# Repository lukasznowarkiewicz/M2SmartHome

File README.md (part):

# M2SmartHome

## Overview

Setting up a smart home hub, such as running Home Assistant, often requires hardware with sufficient performance and connectivity options. Many existing solutions, like Raspberry Pi, may be insufficient for advanced automation tasks due to a low-power CPU or a slow microSD card on which the OS is installed. A good alternative could be an x86 mini PC, but these often lack expansion ports.  

M2SmartHome is an add-on card that operates on PCIe 2.0 x1 and can be installed in any M.2 2280 Key M-equipped device. By integrating multiple essential components into a single device, it eliminates the need for external adapters and additional hardware.  

The device is equipped with onboard eMMC memory, an SD card reader, WiFi 802.11n 2.4GHz radio (RTL8188), and a Thread radio (EFR32) from Silicon Labs. Once installed in an M.2 slot, it provides both storage for the operating system and enhanced connectivity, making it an ideal choice for smart home setups.

## Features

- **Form Factor**: M.2 2280 Key M
- **Interface**: M.2 edge conenctor PCIe 2.0 x1 
- **Storage**: Onboard 16GB eMMC, micro SD card reader
- **Wireless Connectivity**:
  - **WiFi**: 802.11n 2.4GHz (Realtek RTL8188)
  - **Thread Radio**: EFR32MG21 (Silicon Labs)

## Block diagram

On the diagram below siplified system architecture has been presented. PCIe 2.0 x1 interface from host device is connected to PCIe bridge. To four USB 2.0 ports all crucial components are connected: eMMC memory controller, micro SD card controller, USB to UART bridge with Thread / ZigBee RF SOC and WiFi network card. 

### PCie to USB bridge
As a PCIe bridge choosen the `TUSB7340` manufactured by Texas Instruments. `TUSB7340` is a PCIe-to-USB 3.0 host controller with a single line  PCIe interface, compliant with the PCIe  Specification 2.0, supporting programmable driver current, de-emphasis levels, and advanced power management (L0, L0s, L1, L2, L2/L3Ready, L3, D0, D3Hot, D3Cold). It features four USB 3.0 ports as well as USB 2.0 data lines with EHCI (480 Mbps) and OHCI (12 Mbps, 1.5 Mbps) controllers for high-, full-, and low-speed transactions. An EEPROM connected via I²C has been added to enable optional features and configurable settings. Additionally TagConnect TC2030 6-pin connector has been added for flashing I²C EEPROM and TC2050 10-pin connector for accesing `TUSB7340` JTAG.

Components related to this part of the schematic has been highlighted in green on the board view:

### eMMC memory with controller

The `USB2244` is connected to a `TUSB7340` PCIe-to-USB bridge, acting as a USB 2.0-to-eMMC controller for Kingston’s `EMMC16G-MW28-01E10`, with a Microchip `24AA04T-I/OT` EEPROM for optional configuration. The eMMC is powered directly from the M.2 3.3V rail, eliminating the need for an LDO. The eMMC interface uses D0–D8, CMD, and CLK lines, with 49.9kΩ pull-ups on CMD and data lines. The EEPROM is connected via I²C (SCL, SDA) with 4.7kΩ pull-ups, storing configuration settings for the USB controller. This setup provides high-speed eMMC access over USB in an M.2 form factor.

### micro SD card reader and controller

The `USB2244` controller interfaces with a Hirose `DM3AT-SF-PEJM5` push-push microSD card slot and with a Microchip `24AA04T-I/OT` EEPROM for configuration storage. The microSD card is powered by the internal 3.3V regulator of the `USB2244`. The SD interface utilizes CLK, CMD, and D0–D3 lines, with 49.9kΩ pull-ups on CMD and data lines for stable operation. The EEPROM is connected via I²C (SCL, SDA) with 4.7kΩ pull-ups, allowing the `USB2244` to load stored device settings at startup. Additionaly TagConnect TC2030 

### Thread radio

The Silicon Labs EFR32MG21B020F1024IM32-B is a 802.15.4 Thread radio SoC, providing wireless connectivity, while the Silicon Labs CP2102N-A02-GQFN20 acts as a USB-to-UART bridge for communication with a host system. The EFR32MG21 is powered from the M.2 3.3V rail, with its radio interface using an external antenna for Thread communication. The CP2102N is connected via USB 2.0 (D+, D-) to the host via PCIe USB bridge. 

### WiFi radio

The Realtek RTL8188FTV-VC-CG is a WiFi 802.11b/g/n 2.4GHz radio SoC, providing wireless connectivity. It is powered from the M.2 3.3V rail and interfaces with the host system via a USB 2.0 connection. The RF section is connected to an external antenna. 

## Manufacturing

The PCB was manufactured by JLCPCB, using Gerber files generated by the CI job `kicad_release_CI.yml`. The board features a 6-layer design with the standard stack-up `JLC06081H-2116`.

While the board includes a few high-speed signals, such as USB 2.0 and PCIe 2.0, these interfaces are relatively tolerant of signal integrity variations. As a result, impedance maps were not created for this design.

All PCB order settings are detailed below.

Components were sourced via the Octopart API, with OEMSecrets used to optimize the Bill of Materials (BOM) cost. For assembly, SN42Bi58 low-temperature solder paste was applied, and all components were manually placed using tweezers.

The top side of the board was soldered using a UYUE 946C hotplate, with a preheat stage of 1 minute at 100 °C followed by a 2-minute reflow up to 330 °C. The bottom side was soldered using a preheater set to 100 °C and a hot air gun set to 360 °C.

## Required modifications

Rev.1.1.0 is not flawless, a few moodifications are required

- Q5 transistor Drain and Source swap places
- U7 pin 24 decouple connection cut from 3V3
- Add connection U5 RTS pin to U6 PB00 pin 16
- Add connection U5 CTS pin to U6 PB01 pin 15

## Board bring up 

Board bringup starts with visual inspecion, completion check, as well as DNP components check. Removed all shorts and corrected invidual components using soldering iron. 

First powering up - using lab bench power supply connected to +3V3 power bus, with current limit set to 400 mA. 

### Auxilary equipment used for test 

All tests were performed using x86 architecture 64 bit computer. In this case HP EliteDesk 800 G3 USFF. All tests performed using Ubuntu 24.04 LTS. For testing thread and wifi used `LXC LXC1BL4820240722009` 2.4 GHz tuned antennas. 

### PCie USB bridge

After turning on PC, after operating system loads, when prompted in terminal `sudo lspci -vvv | grep -A 80 TUSB`, verbose output of the `lspci` should looks like below. If so PCIe bridge is working and properly detected by the host. 

```bash                                                             
01:00.0 USB controller: Texas Instruments TUSB73x0 SuperSpeed USB 3.0 xHCI Host Controller (rev 02) (prog-if 30 [XHCI])
        Control: I/O- Mem+ BusMaster+ SpecCycle- MemWINV- VGASnoop- ParErr- Stepping- SERR+ FastB2B- DisINTx+                                                                                                                                                                                                         
        Status: Cap+ 66MHz- UDF- FastB2B- ParErr- DEVSEL=fast >TAbort- <TAbort- <MAbort- >SERR- <PERR- INTx-
        Latency: 0, Cache Line Size: 64 bytes
        Interrupt: pin A routed to IRQ 16
        Region 0: Memory at ce900000 (64-bit, non-prefetchable) [size=64K]
        Region 2: Memory at ce910000 (64-bit, non-prefetchable) [size=8K]
        Capabilities: [40] Power Management version 3
                Flags: PMEClk- DSI- D1+ D2+ AuxCurrent=0mA PME(D0+,D1+,D2+,D3hot+,D3cold-)
                Status: D0 NoSoftRst+ PME-Enable- DSel=0 DScale=0 PME-
        Capabilities: [48] MSI: Enable- Count=1/8 Maskable- 64bit+
                Address: 0000000000000000  Data: 0000
        Capabilities: [70] Express (v2) Endpoint, MSI 00
                DevCap: MaxPayload 1024 bytes, PhantFunc 0, Latency L0s unlimited, L1 unlimited
                        ExtTag- AttnBtn- AttnInd- PwrInd- RBE+ FLReset- SlotPowerLimit 25W
                DevCtl: CorrErr+ NonFatalErr+ FatalErr+ UnsupReq+
                        RlxdOrd+ ExtTag- PhantFunc- AuxPwr- NoSnoop-
                        MaxPayload 256 bytes, MaxReadReq 512 bytes
                DevSta: CorrErr- NonFatalErr- FatalErr- UnsupReq- AuxPwr- TransPend-
                LnkCap: Port #0, Speed 5GT/s, Width x1, ASPM L0s L1, Exit Latency L0s <512ns, L1 <64us
                        ClockPM+ Surprise- LLActRep- BwNot- ASPMOptComp-
                LnkCtl: ASPM L0s L1 Enabled; RCB 64 bytes, Disabled- CommClk+
                        ExtSynch- ClockPM+ AutWidDis- BWInt- AutBWInt-
                LnkSta: Speed 5GT/s, Width x1
                        TrErr- Train- SlotClk+ DLActive- BWMgmt- ABWMgmt-
                DevCap2: Completion Timeout: Not Supported, TimeoutDis+ NROPrPrP- LTR-
                         10BitTagComp- 10BitTagReq- OBFF Not Supported, ExtFmt- EETLPPrefix-
                         EmergencyPowerReduction Not Supported, EmergencyPowerReductionInit-
                         FRS- TPHComp- ExtTPHComp-
                         AtomicOpsCap: 32bit- 64bit- 128bitCAS-
                DevCtl2: Completion Timeout: 50us to 50ms, TimeoutDis- LTR- 10BitTagReq- OBFF Disabled,
                         AtomicOpsCtl: ReqEn-
                LnkCtl2: Target Link Speed: 5GT/s, EnterCompliance- SpeedDis-
                         Transmit Margin: Normal Operating Range, EnterModifiedCompliance- ComplianceSOS-
                         Compliance Preset/De-emphasis: -6dB de-emphasis, 0dB preshoot
                LnkSta2: Current De-emphasis Level: -6dB, EqualizationComplete- EqualizationPhase1-
                         EqualizationPhase2- EqualizationPhase3- LinkEqualizationRequest-
                         Retimer- 2Retimers- CrosslinkRes: unsupported
        Capabilities: [c0] MSI-X: Enable+ Count=8 Masked-
                Vector table: BAR=2 offset=00000000
                PBA: BAR=2 offset=00001000
        Capabilities: [100 v2] Advanced Error Reporting
                UESta:  DLP- SDES- TLP- FCP- CmpltTO- CmpltAbrt- UnxCmplt- RxOF- MalfTLP- ECRC- UnsupReq- ACSViol-
                UEMsk:  DLP- SDES- TLP- FCP- CmpltTO- CmpltAbrt- UnxCmplt- RxOF- MalfTLP- ECRC- UnsupReq- ACSViol-
                UESvrt: DLP+ SDES+ TLP- FCP+ CmpltTO- CmpltAbrt- UnxCmplt- RxOF+ MalfTLP+ ECRC- UnsupReq- ACSViol-
                CESta:  RxErr- BadTLP- BadDLLP- Rollover- Timeout- AdvNonFatalErr-
                CEMsk:  RxErr- BadTLP- BadDLLP- Rollover- Timeout- AdvNonFatalErr+
                AERCap: First Error Pointer: 00, ECRCGenCap+ ECRCGenEn- ECRCChkCap+ ECRCChkEn-
                        MultHdrRecCap- MultHdrRecEn- TLPPfxPres- HdrLogCap-
                HeaderLog: 00000000 00000000 00000000 00000000
        Capabilities: [150 v1] Device Serial Number 08-00-28-00-00-20-00-00
        Kernel driver in use: xhci_hcd
        Kernel modules: xhci_pci
```

Additionally also USB HUB should be visible. When prompted `sudo lsusb -vvv | grep -A 80 TUSB` operating system should return similar config to seen below.

```bash
01:00.0 USB controller [0c03]: Texas Instruments TUSB73x0 SuperSpeed USB 3.0 xHCI Host Controller [104c:8241] (rev 02) (prog-if 30 [XHCI])
	Control: I/O- Mem+ BusMaster+ SpecCycle- MemWINV- VGASnoop- ParErr- Stepping- SERR+ FastB2B- DisINTx+
	Status: Cap+ 66MHz- UDF- FastB2B- ParErr- DEVSEL=fast >TAbort- <TAbort- <MAbort- >SERR- <PERR- INTx-
	Latency: 0, Cache Line Size: 64 bytes
	Interrupt: pin A routed to IRQ 16
	Region 0: Memory at ce900000 (64-bit, non-prefetchable) [size=64K]
	Region 2: Memory at ce910000 (64-bit, non-prefetchable) [size=8K]
	Capabilities: [40] Power Management version 3
		Flags: PMEClk- DSI- D1+ D2+ AuxCurrent=0mA PME(D0+,D1+,D2+,D3hot+,D3cold-)
		Status: D0 NoSoftRst+ PME-Enable- DSel=0 DScale=0 PME-
	Capabilities: [48] MSI: Enable- Count=1/8 Maskable- 64bit+
		Address: 0000000000000000  Data: 0000
	Capabilities: [70] Express (v2) Endpoint, MSI 00
		DevCap:	MaxPayload 1024 bytes, PhantFunc 0, Latency L0s unlimited, L1 unlimited
			ExtTag- AttnBtn- AttnInd- PwrInd- RBE+ FLReset- SlotPowerLimit 25W
		DevCtl:	CorrErr+ NonFatalErr+ FatalErr+ UnsupReq+
			RlxdOrd+ ExtTag- PhantFunc- AuxPwr- NoSnoop-
			MaxPayload 256 bytes, MaxReadReq 512 bytes
		DevSta:	CorrErr- NonFatalErr- FatalErr- UnsupReq- AuxPwr- TransPend-
		LnkCap:	Port #0, Speed 5GT/s, Width x1, ASPM L0s L1, Exit Latency L0s <512ns, L1 <64us
			ClockPM+ Surprise- LLActRep- BwNot- ASPMOptComp-
		LnkCtl:	ASPM L0s L1 Enabled; RCB 64 bytes, Disabled- CommClk+
			ExtSynch- ClockPM+ AutWidDis- BWInt- AutBWInt-
		LnkSta:	Speed 5GT/s, Width x1
			TrErr- Train- SlotClk+ DLActive- BWMgmt- ABWMgmt-
		DevCap2: Completion Timeout: Not Supported, TimeoutDis+ NROPrPrP- LTR-
			 10BitTagComp- 10BitTagReq- OBFF Not Supported, ExtFmt- EETLPPrefix-
			 EmergencyPowerReduction Not Supported, EmergencyPowerReductionInit-
			 FRS- TPHComp- ExtTPHComp-
			 AtomicOpsCap: 32bit- 64bit- 128bitCAS-
		DevCtl2: Completion Timeout: 50us to 50ms, TimeoutDis- LTR- 10BitTagReq- OBFF Disabled,
			 AtomicOpsCtl: ReqEn-
		LnkCtl2: Target Link Speed: 5GT/s, EnterCompliance- SpeedDis-
			 Transmit Margin: Normal Operating Range, EnterModifiedCompliance- ComplianceSOS-
			 Compliance Preset/De-emphasis: -6dB de-emphasis, 0dB preshoot
		LnkSta2: Current De-emphasis Level: -6dB, EqualizationComplete- EqualizationPhase1-
			 EqualizationPhase2- EqualizationPhase3- LinkEqualizationRequest-
			 Retimer- 2Retimers- CrosslinkRes: unsupported
	Capabilities: [c0] MSI-X: Enable+ Count=8 Masked-
		Vector table: BAR=2 offset=00000000
		PBA: BAR=2 offset=00001000
	Capabilities: [100 v2] Advanced Error Reporting
		UESta:	DLP- SDES- TLP- FCP- CmpltTO- CmpltAbrt- UnxCmplt- RxOF- MalfTLP- ECRC- UnsupReq- ACSViol-
		UEMsk:	DLP- SDES- TLP- FCP- CmpltTO- CmpltAbrt- UnxCmplt- RxOF- MalfTLP- ECRC- UnsupReq- ACSViol-
		UESvrt:	DLP+ SDES+ TLP- FCP+ CmpltTO- CmpltAbrt- UnxCmplt- RxOF+ MalfTLP+ ECRC- UnsupReq- ACSViol-
		CESta:	RxErr- BadTLP- BadDLLP- Rollover- Timeout- AdvNonFatalErr-
		CEMsk:	RxErr- BadTLP- BadDLLP- Rollover- Timeout- AdvNonFatalErr+
		AERCap:	First Error Pointer: 00, ECRCGenCap+ ECRCGenEn- ECRCChkCap+ ECRCChkEn-
			MultHdrRecCap- MultHdrRecEn- TLPPfxPres- HdrLogCap-
		HeaderLog: 00000000 00000000 00000000 00000000
	Capabilities: [150 v1] Device Serial Number 08-00-28-00-00-20-00-00
	Kernel driver in use: xhci_hcd
	Kernel modules: xhci_pci
```

Additionally may read PCIe config in pure hex form (`sudo lspci -s 01:00 -xxx`) which can be usefull for customization of the controller setting as it directly reflects memory adresses in I2C EEPROM connected to it.
```bash
01:00.0 USB controller: Texas Instruments TUSB73x0 SuperSpeed USB 3.0 xHCI Host Controller (rev 02)
00: 4c 10 41 82 06 05 10 00 02 30 03 0c 10 00 00 00
10: 04 00 90 ce 00 00 00 00 04 00 91 ce 00 00 00 00
20: 00 00 00 00 00 00 00 00 00 00 00 00 00 00 00 00
30: 00 00 00 00 40 00 00 00 00 00 00 00 ff 01 00 00
40: 01 48 03 7e 08 00 00 00 05 70 86 00 00 00 00 00
50: 00 00 00 00 00 00 00 00 00 00 00 00 00 00 00 00
60: 30 20 00 00 00 00 00 00 00 00 00 00 00 00 00 00
70: 10 c0 02 00 c3 8f e8 07 3f 20 00 00 12 3c 07 00
80: 43 01 12 10 00 00 00 00 00 00 00 00 00 00 00 00
90: 00 00 00 00 10 00 00 00 00 00 00 00 00 00 00 00
a0: 02 00 00 00 00 00 00 00 00 00 00 00 00 00 00 00
b0: 00 00 00 00 00 00 0f 00 00 00 00 00 00 00 00 00
c0: 11 00 07 80 02 00 00 00 02 10 00 00 00 00 00 00
d0: 00 00 00 00 ab 0d 00 00 1b 00 00 00 3f 00 00 00
e0: 00 00 00 00 00 00 00 00 00 00 00 00 00 00 00 00
f0: 00 00 00 00 00 00 00 00 00 00 00 00 00 00 00 00
```

Last check is in a tree form if all four USB devices connected to the hub are visible (`sudo lsusb -vt`). 
```bash
/:  Bus 003.Port 001: Dev 001, Class=root_hub, Driver=xhci_hcd/4p, 480M
    ID 1d6b:0002 Linux Foundation 2.0 root hub
    |__ Port 001: Dev 002, If 0, Class=Vendor Specific Class, Driver=rtl8xxxu, 480M
        ID 0bda:f179 Realtek Semiconductor Corp. RTL8188FTV 802.11b/g/n 1T1R 2.4G WLAN Adapter
    |__ Port 002: Dev 003, If 0, Class=Mass Storage, Driver=usb-storage, 480M
        ID 0424:2240 Microchip Technology, Inc. (formerly SMSC) 
    |__ Port 003: Dev 004, If 0, Class=Vendor Specific Class, Driver=cp210x, 12M
        ID 10c4:ea60 Silicon Labs CP210x UART Bridge
    |__ Port 004: Dev 005, If 0, Class=Mass Storage, Driver=usb-storage, 480M
        ID 0424:2240 Microchip Technology, Inc. (formerly SMSC) 
```

### eMMC memory

eMMC controller is connected to fourth port of USB HUB present in PCIe bridge (`sudo lsusb -vt`). Note that exact same chip is used for micro SD card slot, but connected to two.

```bash
/:  Bus 003.Port 001: Dev 001, Class=root_hub, Driver=xhci_hcd/4p, 480M
    ID 1d6b:0002 Linux Foundation 2.0 root hub
    |__ Port 001: Dev 002, If 0, Class=Vendor Specific Class, Driver=rtl8xxxu, 480M
        ID 0bda:f179 Realtek Semiconductor Corp. RTL8188FTV 802.11b/g/n 1T1R 2.4G WLAN Adapter
    |__ Port 002: Dev 003, If 0, Class=Mass Storage, Driver=usb-storage, 480M
        ID 0424:2240 Microchip Technology, Inc. (formerly SMSC) 
    |__ Port 003: Dev 004, If 0, Class=Vendor Specific Class, Driver=cp210x, 12M
        ID 10c4:ea60 Silicon Labs CP210x UART Bridge
    |__ Port 004: Dev 005, If 0, Class=Mass Storage, Driver=usb-storage, 480M
        ID 0424:2240 Microchip Technology, Inc. (formerly SMSC) <---------------------------
```

It's configuration can be read using `lsusb -d 0424:2240 -vvv` and should be similar to the one below.

```bash
Bus 001 Device 008: ID 0424:2240 Microchip Technology, Inc. (formerly SMSC) Ultra Fast Media
Couldn't open device, some information will be missing
Device Descriptor:
bLength 18
bDescriptorType 1
bcdUSB 2.00
bDeviceClass 0 [unknown]
bDeviceSubClass 0 [unknown]
bDeviceProtocol 0
bMaxPacketSize0 64
idVendor 0x0424 Microchip Technology, Inc. (formerly SMSC)
idProduct 0x2240 Ultra Fast Media
bcdDevice 1.98
iManufacturer 1 Generic
iProduct 2 Ultra Fast Media
iSerial 3 000000225001
bNumConfigurations 1
Configuration Descriptor:
bLength 9
bDescriptorType 2
wTotalLength 0x0020
bNumInterfaces 1
bConfigurationValue 1
iConfiguration 0
bmAttributes 0x80
(Bus Powered)
MaxPower 96mA
Interface Descriptor:
bLength 9
bDescriptorType 4
bInterfaceNumber 0
bAlternateSetting 0
bNumEndpoints 2
bInterfaceClass 8 Mass Storage
bInterfaceSubClass 6 SCSI
bInterfaceProtocol 80 Bulk-Only
iInterface 0
Endpoint Descriptor:
bLength 7
bDescriptorType 5
bEndpointAddress 0x02 EP 2 OUT
bmAttributes 2
Transfer Type Bulk
Synch Type None
Usage Type Data
wMaxPacketSize 0x0200 1x 512 bytes
bInterval 1
Endpoint Descriptor:
bLength 7
bDescriptorType 5
bEndpointAddress 0x82 EP 2 IN
bmAttributes 2
Transfer Type Bulk
Synch Type None
Usage Type Data
wMaxPacketSize 0x0200 1x 512 bytes
bInterval 0

```

If eMMC memory connected to controller is seen properly it should be listed as block device `lsblk` with correct memory - something below 16GB.

```bash
NAME MAJ:MIN RM SIZE RO TYPE MOUNTPOINTS
sdb 8:16 1 14.6G 0 disk
```

Additionally, it's recommended to check kernel debug messages during system startup to ensure no errors were reported. This can be done using the command: `sudo dmesg`.

```bash
[ 2402.769465] usb 1-13: new high-speed USB device number 8 using xhci_hcd
[ 2402.902304] usb 1-13: New USB device found, idVendor=0424, idProduct=2240, bcdDevice= 1.98
[ 2402.902327] usb 1-13: New USB device strings: Mfr=1, Product=2, SerialNumber=3
[ 2402.902335] usb 1-13: Product: Ultra Fast Media
[ 2402.902341] usb 1-13: Manufacturer: Generic
[ 2402.902347] usb 1-13: SerialNumber: 000000225001
[ 2402.907570] usb-storage 1-13:1.0: USB Mass Storage device detected
[ 2402.907866] scsi host2: usb-storage 1-13:1.0
[ 2403.963071] scsi 2:0:0:0: Direct-Access Generic Ultra HS-COMBO 1.98 PQ: 0 ANSI: 0
[ 2403.963267] sd 2:0:0:0: Attached scsi generic sg1 type 0
[ 2403.969432] sd 2:0:0:0: [sdb] 30615552 512-byte logical blocks: (15.7 GB/14.6 GiB)
[ 2403.970000] sd 2:0:0:0: [sdb] Write Protect is off
[ 2403.970004] sd 2:0:0:0: [sdb] Mode Sense: 23 00 00 00
[ 2403.970608] sd 2:0:0:0: [sdb] No Caching mode page found
[ 2403.970611] sd 2:0:0:0: [sdb] Assuming drive cache: write through
[ 2403.974170] sd 2:0:0:0: [sdb] Attached SCSI removable disk
```

It is recommended to quickly benchmark the memory using Gnome Disks tool, as inproperly solder may result in lower read/write speeds. The expected average read speed around 33MB/s and average access time below 1 ms. 

For more detailed benchmark used KDiskMark, which have option to select test file size and generate different write/read patterns beeing closer to more real life scenario. 

For complete test may use `badblocks` as a extended write/read test which took aproximately 6 hours. Application writes patterns to the entire memory surface and checks if all data has been written correctly. Usage `sudo badblocks -wsv /dev/sdX`
```bash 
Checking for bad blocks in read-write mode
From block 0 to 15307775
Testing with pattern 0xaa: done                                                 
Reading and comparing: done                                                 
Testing with pattern 0x55: done                                                 
Reading and comparing: done                                                 
Testing with pattern 0xff: done                                                 
Reading and comparing: done                                                 
Testing with pattern 0x00: done                                                 
Reading and comparing: done                                                 
Pass completed, 0 bad blocks found. (0/0/0 errors)
```

### uSD reader

uSD controller is connected to second port of USB HUB present in PCIe bridge (`sudo lsusb -vt`).

```bash
/:  Bus 003.Port 001: Dev 001, Class=root_hub, Driver=xhci_hcd/4p, 480M
    ID 1d6b:0002 Linux Foundation 2.0 root hub
    |__ Port 001: Dev 002, If 0, Class=Vendor Specific Class, Driver=rtl8xxxu, 480M
        ID 0bda:f179 Realtek Semiconductor Corp. RTL8188FTV 802.11b/g/n 1T1R 2.4G WLAN Adapter
    |__ Port 002: Dev 003, If 0, Class=Mass Storage, Driver=usb-storage, 480M
        ID 0424:2240 Microchip Technology, Inc. (formerly SMSC) <---------------------------
    |__ Port 003: Dev 004, If 0, Class=Vendor Specific Class, Driver=cp210x, 12M
        ID 10c4:ea60 Silicon Labs CP210x UART Bridge
    |__ Port 004: Dev 005, If 0, Class=Mass Storage, Driver=usb-storage, 480M
        ID 0424:2240 Microchip Technology, Inc. (formerly SMSC) 
```

It's configuration can be read using `lsusb -d 0424:2240 -vvv` and should be similar to the one below.

```bash
Bus 003 Device 003: ID 0424:2240 Microchip Technology, Inc. (formerly SMSC) Ultra Fast Media
Couldn't open device, some information will be missing
Device Descriptor:
bLength 18
bDescriptorType 1
bcdUSB 2.00
bDeviceClass 0 [unknown]
bDeviceSubClass 0 [unknown]
bDeviceProtocol 0
bMaxPacketSize0 64
idVendor 0x0424 Microchip Technology, Inc. (formerly SMSC)
idProduct 0x2240 Ultra Fast Media
bcdDevice 1.98
iManufacturer 1 Generic
iProduct 2 Ultra Fast Media
iSerial 3 000000225001
bNumConfigurations 1
Configuration Descriptor:
bLength 9
bDescriptorType 2
wTotalLength 0x0020
bNumInterfaces 1
bConfigurationValue 1
iConfiguration 0
bmAttributes 0x80
(Bus Powered)
MaxPower 96mA
Interface Descriptor:
bLength 9
bDescriptorType 4
bInterfaceNumber 0
bAlternateSetting 0
bNumEndpoints 2
bInterfaceClass 8 Mass Storage
bInterfaceSubClass 6 SCSI
bInterfaceProtocol 80 Bulk-Only
iInterface 0
Endpoint Descriptor:
bLength 7
bDescriptorType 5
bEndpointAddress 0x02 EP 2 OUT
bmAttributes 2
Transfer Type Bulk
Synch Type None
Usage Type Data
wMaxPacketSize 0x0200 1x 512 bytes
bInterval 1
Endpoint Descriptor:
bLength 7
bDescriptorType 5
bEndpointAddress 0x82 EP 2 IN
bmAttributes 2
Transfer Type Bulk
Synch Type None
Usage Type Data
wMaxPacketSize 0x0200 1x 512 bytes
bInterval 0
```

Insert micro SD card into slot (it is hot pluggable, may be connected when powered on). If uSD memory connected to controller is seen properly it should be listed as block device `lsblk` with correct memory - corresponding to the size of inserted card.

```bash
NAME MAJ:MIN RM SIZE RO TYPE MOUNTPOINTS
sdb 8:16 1 3.7G 0 disk
└─sdb1 8:17 1 3.7G 0 part /media/user/9016-4EF8
```

Additionally, it's recommended to check kernel debug messages during system startup to ensure no errors were reported. This can be done using the command: `sudo dmesg`. Messages with connected just empty reader:
```bash
[ 33.892694] usb 1-13: new high-speed USB device number 5 using xhci_hcd
[ 34.027971] usb 1-13: New USB device found, idVendor=0424, idProduct=2240, bcdDevice= 1.98
[ 34.027977] usb 1-13: New USB device strings: Mfr=1, Product=2, SerialNumber=3
[ 34.027979] usb 1-13: Product: Ultra Fast Media
[ 34.027981] usb 1-13: Manufacturer: Generic
[ 34.027983] usb 1-13: SerialNumber: 000000225001
[ 34.051629] usb-storage 1-13:1.0: USB Mass Storage device detected
[ 34.051918] scsi host2: usb-storage 1-13:1.0
[ 34.052013] usbcore: registered new interface driver usb-storage
[ 34.054051] usbcore: registered new interface driver uas
[ 35.074189] scsi 2:0:0:0: Direct-Access Generic Ultra HS-COMBO 1.98 PQ: 0 ANSI: 0
[ 35.074516] sd 2:0:0:0: Attached scsi generic sg1 type 0
[ 35.075325] sd 2:0:0:0: [sdb] Media removed, stopped polling
[ 35.075721] sd 2:0:0:0: [sdb] Attached SCSI removable disk
```

`dmesg` when inserted 4GB micro SD card:
```bash
[ 651.529877] sd 2:0:0:0: [sdb] 7759872 512-byte logical blocks: (3.97 GB/3.70 GiB)
[ 651.531210] sdb: detected capacity change from 0 to 7759872
[ 651.532979] sdb: sdb1
```

Benchmarked using Gnome Disks tool. Tested 3 different uSD cards. 
  1. Off brand 4GB class 4 micro SD card 

  2. ATP 1GB SLC industrial micro SD card:

  3. San Disk Extreme 32GB class Ultra 3:

For more detailed benchmark used KDiskMark, which have option to select test file size and generate different write/read patterns beeing closer to more real life scenario. 

For complete stability test may use `badblocks` as a extended write/read test which took aproximately 6 hours. Application writes patterns to the entire memory surface and checks if all data has been written correctly. Usage `sudo badblocks -wsv /dev/sdX`
```bash
Checking for bad blocks in read-write mode
From block 0 to 31154687
Testing with pattern 0xaa: done                                                 
Reading and comparing: done                                                 
Testing with pattern 0x55: done                                                 
Reading and comparing: done                                                 
Testing with pattern 0xff: done                                                 
Reading and comparing: done                                                 
Testing with pattern 0x00: done                                                 
Reading and comparing: done                                                 
Pass completed, 0 bad blocks found. (0/0/0 errors)
```

### Thread radio

Thread radio consist of two main parts USB UART converter and Thread Radio chip. 

USB UART controller is connected to the third port of USB HUB present in PCIe bridge (`sudo lsusb -vt`).

```bash
/:  Bus 003.Port 001: Dev 001, Class=root_hub, Driver=xhci_hcd/4p, 480M
    ID 1d6b:0002 Linux Foundation 2.0 root hub
    |__ Port 001: Dev 002, If 0, Class=Vendor Specific Class, Driver=rtl8xxxu, 480M
        ID 0bda:f179 Realtek Semiconductor Corp. RTL8188FTV 802.11b/g/n 1T1R 2.4G WLAN Adapter
    |__ Port 002: Dev 003, If 0, Class=Mass Storage, Driver=usb-storage, 480M
        ID 0424:2240 Microchip Technology, Inc. (formerly SMSC) 
    |__ Port 003: Dev 004, If 0, Class=Vendor Specific Class, Driver=cp210x, 12M
        ID 10c4:ea60 Silicon Labs CP210x UART Bridge <---------------------------------------
    |__ Port 004: Dev 005, If 0, Class=Mass Storage, Driver=usb-storage, 480M
        ID 0424:2240 Microchip Technology, Inc. (formerly SMSC) 
```

It's configuration can be read using `lsusb -d 10c4:ea60 -vvv` and should be similar to the one below.

```bash
Bus 003 Device 004: ID 10c4:ea60 Silicon Labs CP210x UART Bridge
Device Descriptor:
  bLength                18
  bDescriptorType         1
  bcdUSB               2.00
  bDeviceClass            0 [unknown]
  bDeviceSubClass         0 [unknown]
  bDeviceProtocol         0 
  bMaxPacketSize0        64
  idVendor           0x10c4 Silicon Labs
  idProduct          0xea60 CP210x UART Bridge
  bcdDevice            1.00
  iManufacturer           1 Silicon Labs
  iProduct                2 CP2102N USB to UART Bridge Controller
  iSerial                 3 9ac4a9c38069ed11b176ea8cedc06881
  bNumConfigurations      1
  Configuration Descriptor:
    bLength                 9
    bDescriptorType         2
    wTotalLength       0x0020
    bNumInterfaces          1
    bConfigurationValue     1
    iConfiguration          0 
    bmAttributes         0x80
      (Bus Powered)
    MaxPower              100mA
    Interface Descriptor:
      bLength                 9
      bDescriptorType         4
      bInterfaceNumber        0
      bAlternateSetting       0
      bNumEndpoints           2
      bInterfaceClass       255 Vendor Specific Class
      bInterfaceSubClass      0 [unknown]
      bInterfaceProtocol      0 
      iInterface              0 
      Endpoint Descriptor:
        bLength                 7
        bDescriptorType         5
        bEndpointAddress     0x02  EP 2 OUT
        bmAttributes            2
can't get device qualifier: Resource temporarily unavailable
can't get debug descriptor: Resource temporarily unavailable
can't get debug descriptor: Resource temporarily unavailable
          Transfer Type            Bulk
          Synch Type               None
          Usage Type               Data
        wMaxPacketSize     0x0040  1x 64 bytes
        bInterval               0
      Endpoint Descriptor:
        bLength                 7
        bDescriptorType         5
        bEndpointAddress     0x82  EP 2 IN
        bmAttributes            2
          Transfer Type            Bulk
          Synch Type               None
          Usage Type               Data
        wMaxPacketSize     0x0040  1x 64 bytes
        bInterval               0
Device Status:     0x0000
  (Bus Powered)
```

For basic check of EFR32MG21 thread radio module have to probe it through SWD. For this test use FTDI FT2232C/H, with 470 ohm resistor between TDI and TDO pins. 
```bash
FTDI                          Target
# ----                          ------
# 1  - Vref   ----------------- Vcc
# 3  - nTRST  -
# 4  - GND    ----------------- GND
# 5  - TDI    ---/\470 Ohm/\--- SWDIO
# 7  - TMS    -
# 9  - TCK    ----------------- SWCLK
# 11 - RTCK   -
# 13 - TDO    ----------------- SWDIO
# 15 - nSRST  - - - - - - - - - nRESET
```
Configuration file for OpenOCD is located in the firmware/thread/OpenOCD folder. For probing use TagConnect TC2030 cable and connect it to J9 port on the PCB. 
Command for probing: `openocd -f ft2232_efr32.cfg -f target/efm32.cfg` (note efm32 is not the desired chip, but this config allows probe of the efr32)
Expected result:
```bash
Open On-Chip Debugger 0.12.0
Licensed under GNU GPL v2
For bug reports, read
	http://openocd.org/doc/doxygen/bugs.html
Info : FTDI SWD mode enabled
cortex_m reset_config sysresetreq

Info : Listening on port 6666 for tcl connections
Info : Listening on port 4444 for telnet connections
Info : clock speed 1000 kHz
Info : SWD DPIDR 0x6ba02477
Info : [efm32.cpu] Cortex-M33 r0p3 processor detected
Info : [efm32.cpu] target has 8 breakpoints, 4 watchpoints
Info : starting gdb server for efm32.cpu on 3333
Info : Listening on port 3333 for gdb connections
Error: [efm32.cpu] clearing lockup after double fault
Polling target efm32.cpu failed, trying to reexamine
Info : [efm32.cpu] Cortex-M33 r0p3 processor detected
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
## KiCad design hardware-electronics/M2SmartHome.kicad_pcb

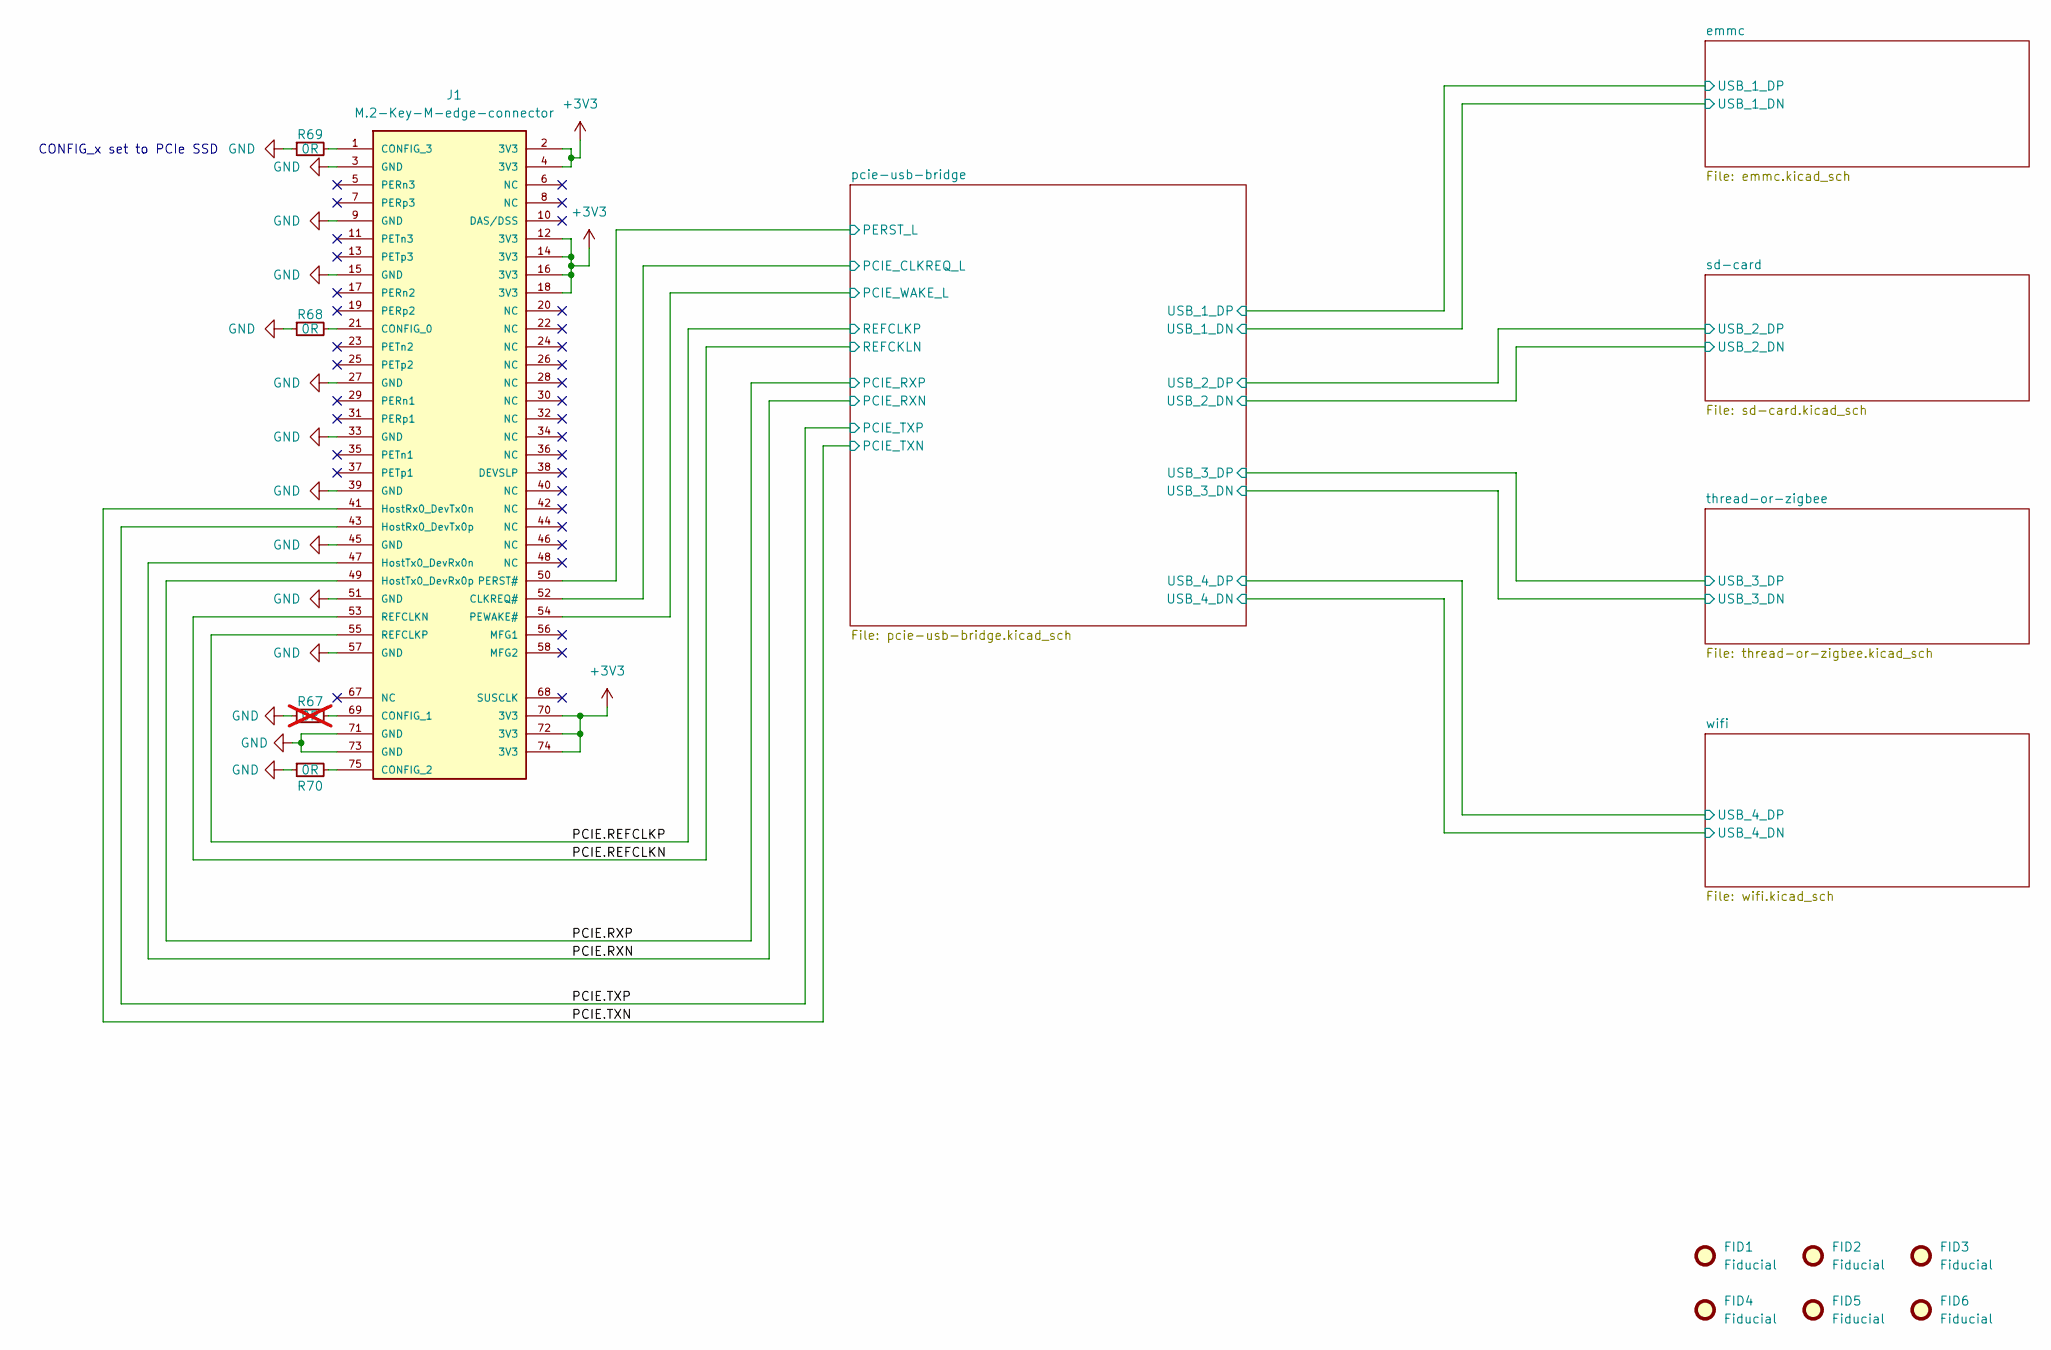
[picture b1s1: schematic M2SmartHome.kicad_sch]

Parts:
FID1, FID2, FID3, FID4, FID5, FID6: Fiducial; Fiducial_0.5mm_Mask1mm
J1: M.2-Key-M-edge-connector
R67: R_0_0402; R_0402; MPN CRCW04020000Z0ED; not fitted
R68, R69, R70: R_0_0402; R_0402; MPN CRCW04020000Z0ED

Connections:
+3V3: J1.2 (3V3), J1.4 (3V3), J1.12 (3V3), J1.14 (3V3), J1.16 (3V3), J1.18 (3V3), J1.70 (3V3), J1.72 (3V3), J1.74 (3V3); also elsewhere on the board
/PCIE.REFCLKN: J1.53 (REFCLKN); also elsewhere on the board
/PCIE.REFCLKP: J1.55 (REFCLKP); also elsewhere on the board
/PCIE.RXN: J1.47 (HostTx0_DevRx0n); also elsewhere on the board
/PCIE.RXP: J1.49 (HostTx0_DevRx0p); also elsewhere on the board
/PCIE.TXN: J1.41 (HostRx0_DevTx0n); also elsewhere on the board
/PCIE.TXP: J1.43 (HostRx0_DevTx0p); also elsewhere on the board
/pcie-usb-bridge/PCIE_CLKREQ_L: J1.52 (CLKREQ#); also elsewhere on the board
/pcie-usb-bridge/PCIE_WAKE_L: J1.54 (PEWAKE#); also elsewhere on the board
/pcie-usb-bridge/PERST_L: J1.50 (PERST#); also elsewhere on the board
GND: J1.3 (GND), J1.9 (GND), J1.15 (GND), J1.27 (GND), J1.33 (GND), J1.39 (GND), J1.45 (GND), J1.51 (GND), J1.57 (GND), J1.71 (GND), J1.73 (GND), R67.1, R68.1, R69.1, R70.1; also elsewhere on the board
unnamed: J1.21 (CONFIG_0), R68.2
unnamed: J1.69 (CONFIG_1), R67.2
unnamed: J1.75 (CONFIG_2), R70.2
unnamed: J1.1 (CONFIG_3), R69.2

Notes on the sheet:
CONFIG_x set to PCIe SSD

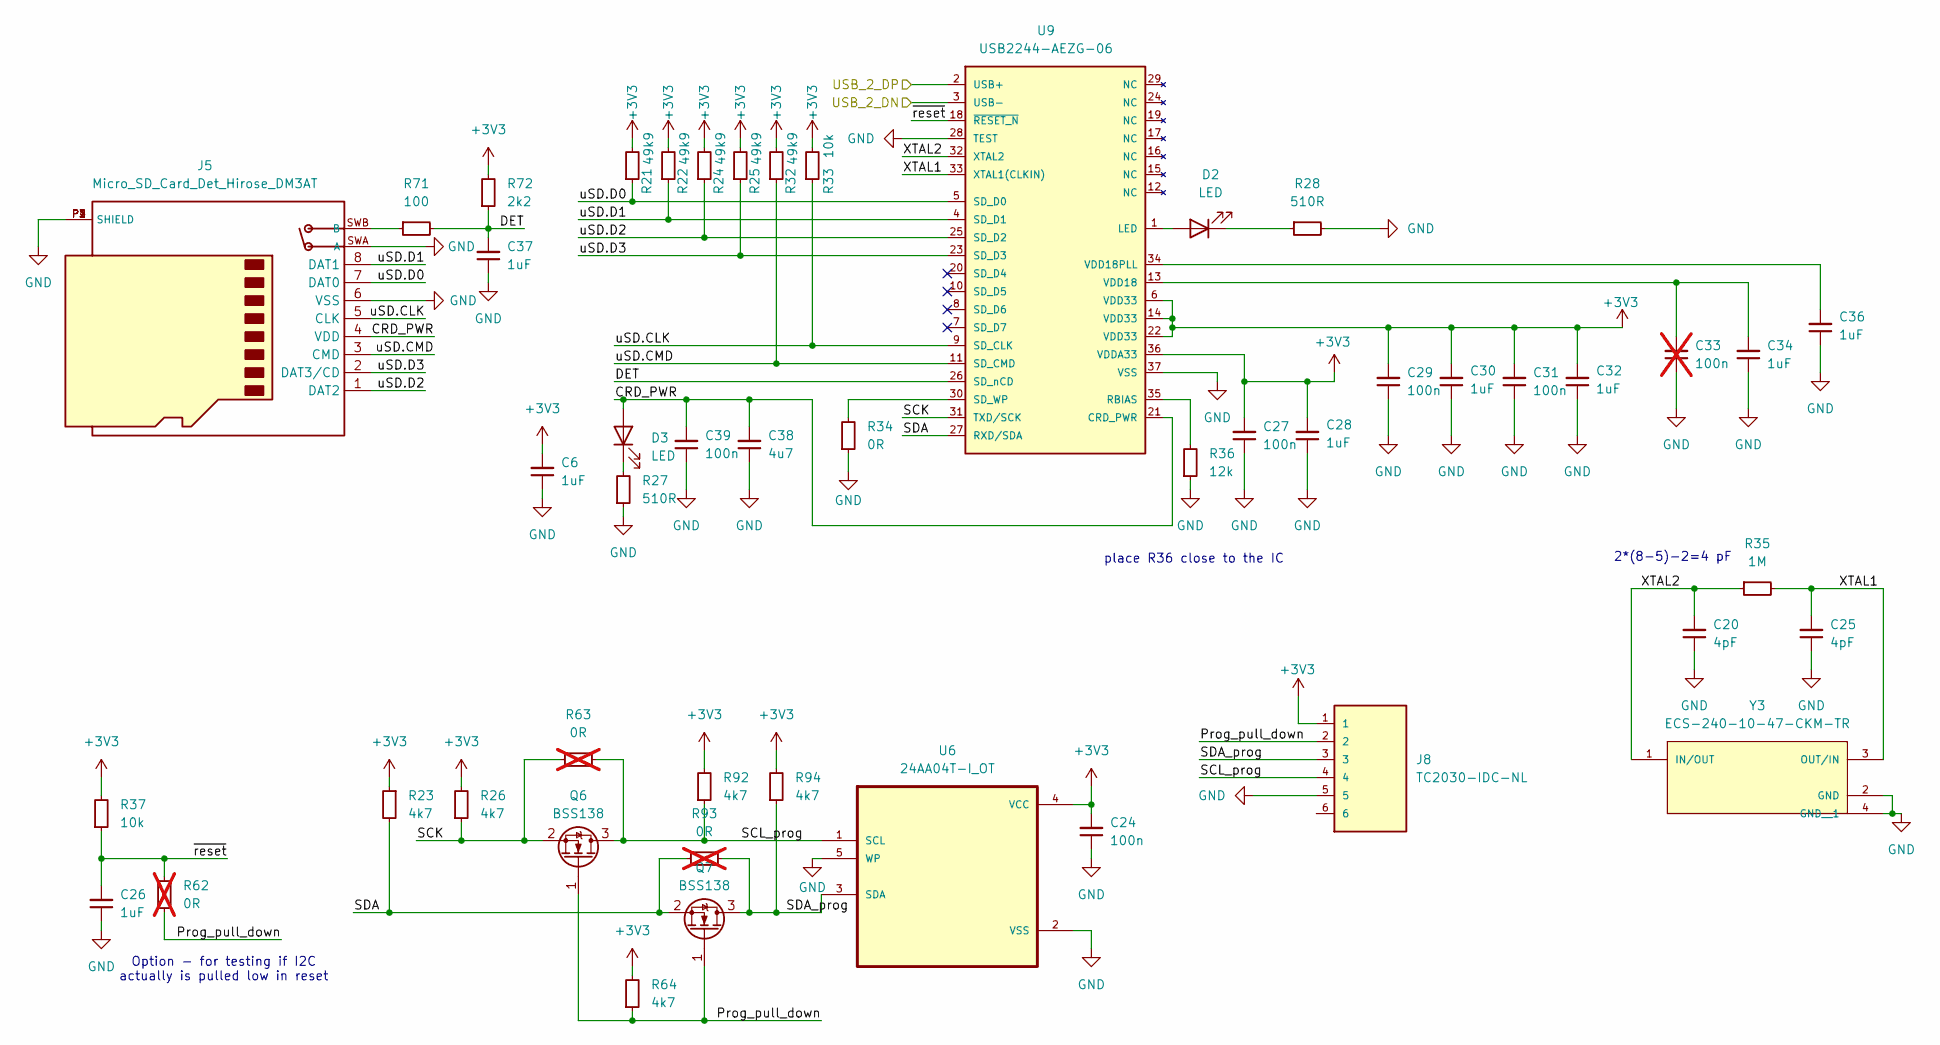
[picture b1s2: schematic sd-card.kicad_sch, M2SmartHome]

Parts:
C6, C26, C28, C30, C32, C34, C36, C37: C_1uF_0402; C_0402; Voltage 50V; MPN GRM155R61H105KE05D
C20, C25: C_4pF_0402; C_0402; Voltage 50V; MPN GRM1555C1H4R0CA01D
C24, C27, C29, C31, C39: C_100n_0402; C_0402; Voltage 10V; MPN GRM155R61A104KA01D
C33: C_100n_0402; C_0402; Voltage 10V; MPN GRM155R61A104KA01D; not fitted
C38: C_4u7_0402; C_0402; Voltage 6.3V; MPN GRM155R60J475ME47D
D2, D3: LED; LED_KPT-1608ZGC
J5: Micro_SD_Card_Det_Hirose_DM3AT; HRS_DM3AT-SF-PEJM5; MPN DM3AT-SF-PEJM5
J8: TC2030-IDC-NL; TAG_TC2030-IDC-NL; PARTREV MS
Q6, Q7: BSS138; SOT-23
R21, R22, R24, R25, R32: R_49k9_0402; R_0402; Tolerance 1%; MPN CRCW040249K9FKED
R23, R26, R64, R92, R94: R_4k7_0402; R_0402; Tolerance 1%; MPN CRCW04024K70FKED
R27, R28: R_510R_0402; R_0402; Tolerance 1%; MPN CRCW0402510RJNED
R33, R37: R_10k_0402; R_0402; Tolerance 1%; MPN CRCW040210K0FKED
R34: R_0_0402; R_0402; MPN CRCW04020000Z0ED
R35: R_1M_0402; R_0402; Tolerance 1%; MPN CRCW04021M00FKED
R36: R_12k_0402; R_0402; Tolerance 1%; Voltage 50V; MPN CRCW040212K0FKTDBC
R62, R63, R93: R_0_0402; R_0402; MPN CRCW04020000Z0ED; not fitted
R71: R_100_0402; R_0402; Tolerance 1%; MPN CRCW0402100RFKED
R72: R_2k2_0402; R_0402; Tolerance 1%; MPN CRCW04022K20FKED
U6: 24AA04T-I_OT
U9: USB2244-AEZG-06
Y3: ECS-240-10-47-CKM-TR; PARTREV 2017

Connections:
+3V3: C6.2, C24.2, C27.2, C28.2, C29.2, C30.2, C31.2, C32.2, J8.1, R21.2, R22.2, R23.1, R24.2, R25.2, R26.2, R32.2, R33.2, R37.2, R64.2, R72.2, R92.2, R94.2, U6.4 (VCC), U9.6 (VDD33), U9.14 (VDD33), U9.22 (VDD33), U9.36 (VDDA33); also elsewhere on the board
/pcie-usb-bridge/USB_2_DN: U9.3 (USB-); also elsewhere on the board
/pcie-usb-bridge/USB_2_DP: U9.2 (USB+); also elsewhere on the board
/sd-card/CRD_PWR: C38.2, C39.2, D3.2 (A), J5.4 (VDD), U9.21 (CRD_PWR)
/sd-card/DET: C37.2, R71.2, R72.1, U9.26 (SD_nCD)
/sd-card/Prog_pull_down: J8.2, Q6.1 (G), Q7.1 (G), R62.2, R64.1
/sd-card/SCK: Q6.2 (S), R26.1, R63.2, U9.31 (TXD/SCK)
/sd-card/SCL_prog: J8.4, Q6.3 (D), R63.1, R92.1, U6.1 (SCL)
/sd-card/SDA: Q7.2 (S), R23.2, R93.2, U9.27 (RXD/SDA)
/sd-card/SDA_prog: J8.3, Q7.3 (D), R93.1, R94.1, U6.3 (SDA)
/sd-card/XTAL1: C25.2, R35.2, U9.33 (XTAL1(CLKIN)), Y3.3 (OUT/IN)
/sd-card/XTAL2: C20.2, R35.1, U9.32 (XTAL2), Y3.1 (IN/OUT)
/sd-card/uSD.CLK: J5.5 (CLK), R33.1, U9.9 (SD_CLK)
/sd-card/uSD.CMD: J5.3 (CMD), R32.1, U9.11 (SD_CMD)
/sd-card/uSD.D0: J5.7 (DAT0), R21.1, U9.5 (SD_D0)
/sd-card/uSD.D1: J5.8 (DAT1), R22.1, U9.4 (SD_D1)
/sd-card/uSD.D2: J5.1 (DAT2), R24.1, U9.25 (SD_D2)
/sd-card/uSD.D3: J5.2 (DAT3/CD), R25.1, U9.23 (SD_D3)
/sd-card/~reset: C26.2, R37.1, R62.1, U9.18 (~RESET_N)
GND: C6.1, C20.1, C24.1, C25.1, C26.1, C27.1, C28.1, C29.1, C30.1, C31.1, C32.1, C33.1, C34.1, C36.1, C37.1, C38.1, C39.1, J5.6 (VSS), J5.P1 (SHIELD), J5.P2 (SHIELD), J5.P3 (SHIELD), J5.P4 (SHIELD), J5.SWA (A), J8.5, R27.1, R28.2, R34.1, R36.1, U6.2 (VSS), U6.5 (WP), U9.28 (TEST), U9.37 (VSS), Y3.2 (GND), Y3.4 (GND__1); also elsewhere on the board
unnamed: D2.2 (A), U9.1 (LED)
unnamed: D2.1 (K), R28.1
unnamed: D3.1 (K), R27.2
unnamed: J5.SWB (B), R71.1
unnamed: R36.2, U9.35 (RBIAS)
unnamed: R34.2, U9.30 (SD_WP)
unnamed: C33.2, C34.2, U9.13 (VDD18)
unnamed: C36.2, U9.34 (VDD18PLL)

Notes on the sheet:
Option - for testing if I2C actually is pulled low in reset
place R36 close to the IC
2*(8-5)-2=4 pF

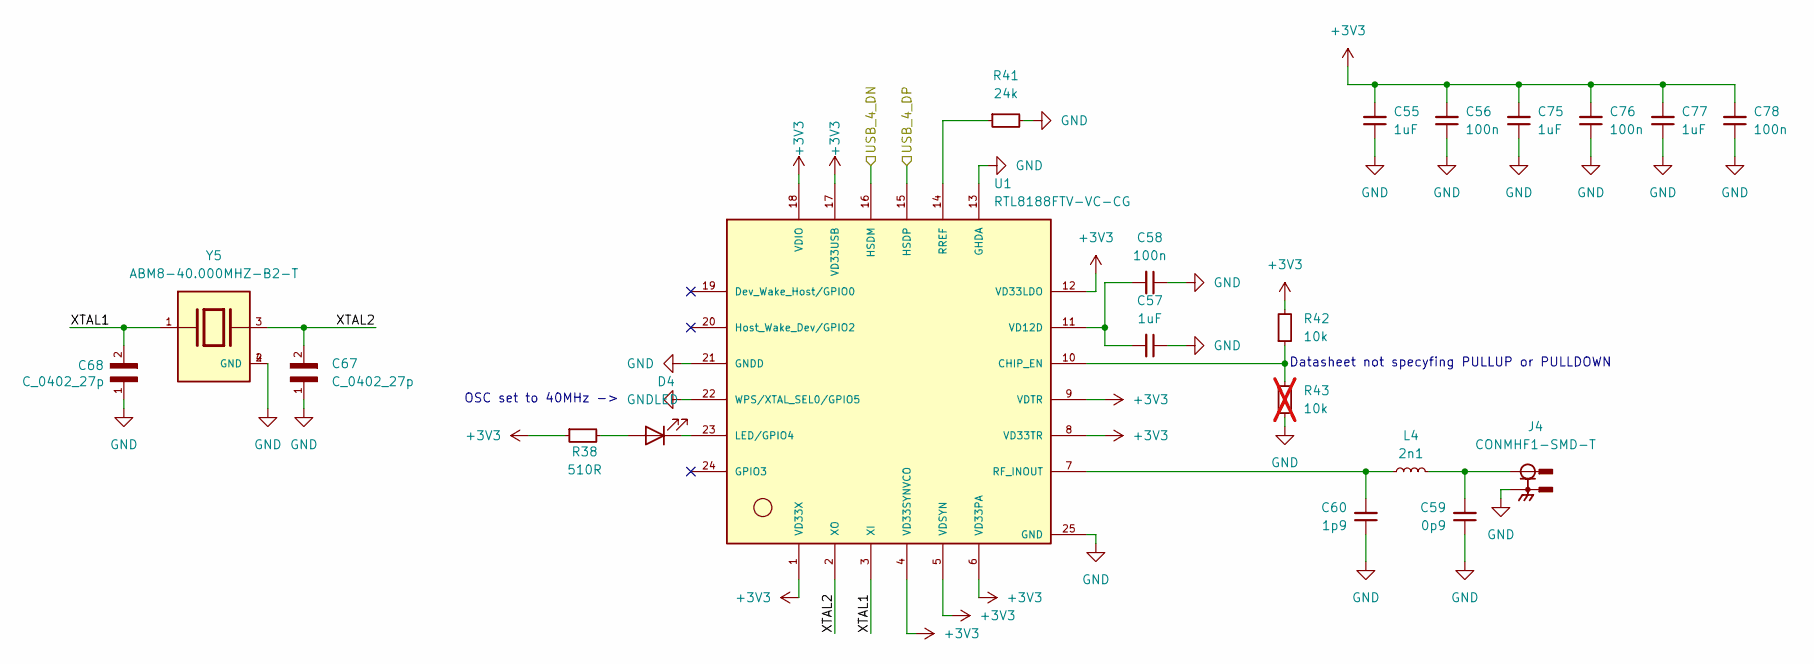
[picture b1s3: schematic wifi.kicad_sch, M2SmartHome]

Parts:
C55, C57, C75, C77: C_1uF_0402; C_0402; Voltage 50V; MPN GRM155R61H105KE05D
C56, C58, C76, C78: C_100n_0402; C_0402; Voltage 10V; MPN GRM155R61A104KA01D
C59: C_0p9_0201; C_0201; Voltage 50V; MPN GRM0335C1HR90WA01D
C60: C_1p9_0201; C_0201; Voltage 50V; MPN GRM0335C1H1R9WA01D
C67, C68: C_0402_27p; C_0402
D4: LED; LED_KPT-1608ZGC
J4: CONMHF1-SMD-T
L4: L_2n1_0201; L_0201; MPN LQP03HQ2N1B02D
R38: R_510R_0402; R_0402; Tolerance 1%; MPN CRCW0402510RJNED
R41: R_24k_0402; R_0402; Tolerance 1%; MPN CRCW040224K0FKED
R42: R_10k_0402; R_0402; Tolerance 1%; MPN CRCW040210K0FKED
R43: R_10k_0402; R_0402; Tolerance 1%; MPN CRCW040210K0FKED; not fitted
U1: RTL8188FTV-VC-CG; PART_REV 1.1
Y5: ABM8-40.000MHZ-B2-T; PARTREV 44041

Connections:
+3V3: C55.2, C56.2, C75.2, C76.2, C77.2, C78.2, R38.1, R42.2, U1.1 (VD33X), U1.4 (VD33SYNVCO), U1.5 (VDSYN), U1.6 (VD33PA), U1.8 (VD33TR), U1.9 (VDTR), U1.12 (VD33LDO), U1.17 (VD33USB), U1.18 (VDIO); also elsewhere on the board
/pcie-usb-bridge/USB_4_DN: U1.16 (HSDM); also elsewhere on the board
/pcie-usb-bridge/USB_4_DP: U1.15 (HSDP); also elsewhere on the board
/wifi/XTAL1: C68.2, U1.3 (XI), Y5.1
/wifi/XTAL2: C67.2, U1.2 (XO), Y5.3
GND: C55.1, C56.1, C57.1, C58.1, C59.1, C60.1, C67.1, C68.1, C75.1, C76.1, C77.1, C78.1, J4.S1, J4.S2, J4.S3, R41.2, R43.1, U1.13 (GHDA), U1.21 (GNDD), U1.22 (WPS/XTAL_SEL0/GPIO5), U1.25 (GND), Y5.2 (GND), Y5.4 (GND); also elsewhere on the board
unnamed: C59.2, J4.1, L4.1
unnamed: D4.2 (A), R38.2
unnamed: D4.1 (K), U1.23 (LED/GPIO4)
unnamed: R42.1, R43.2, U1.10 (CHIP_EN)
unnamed: C60.2, L4.2, U1.7 (RF_INOUT)
unnamed: R41.1, U1.14 (RREF)
unnamed: C57.2, C58.2, U1.11 (VD12D)

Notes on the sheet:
Datasheet not specyfing PULLUP or PULLDOWN
OSC set to 40MHz ->

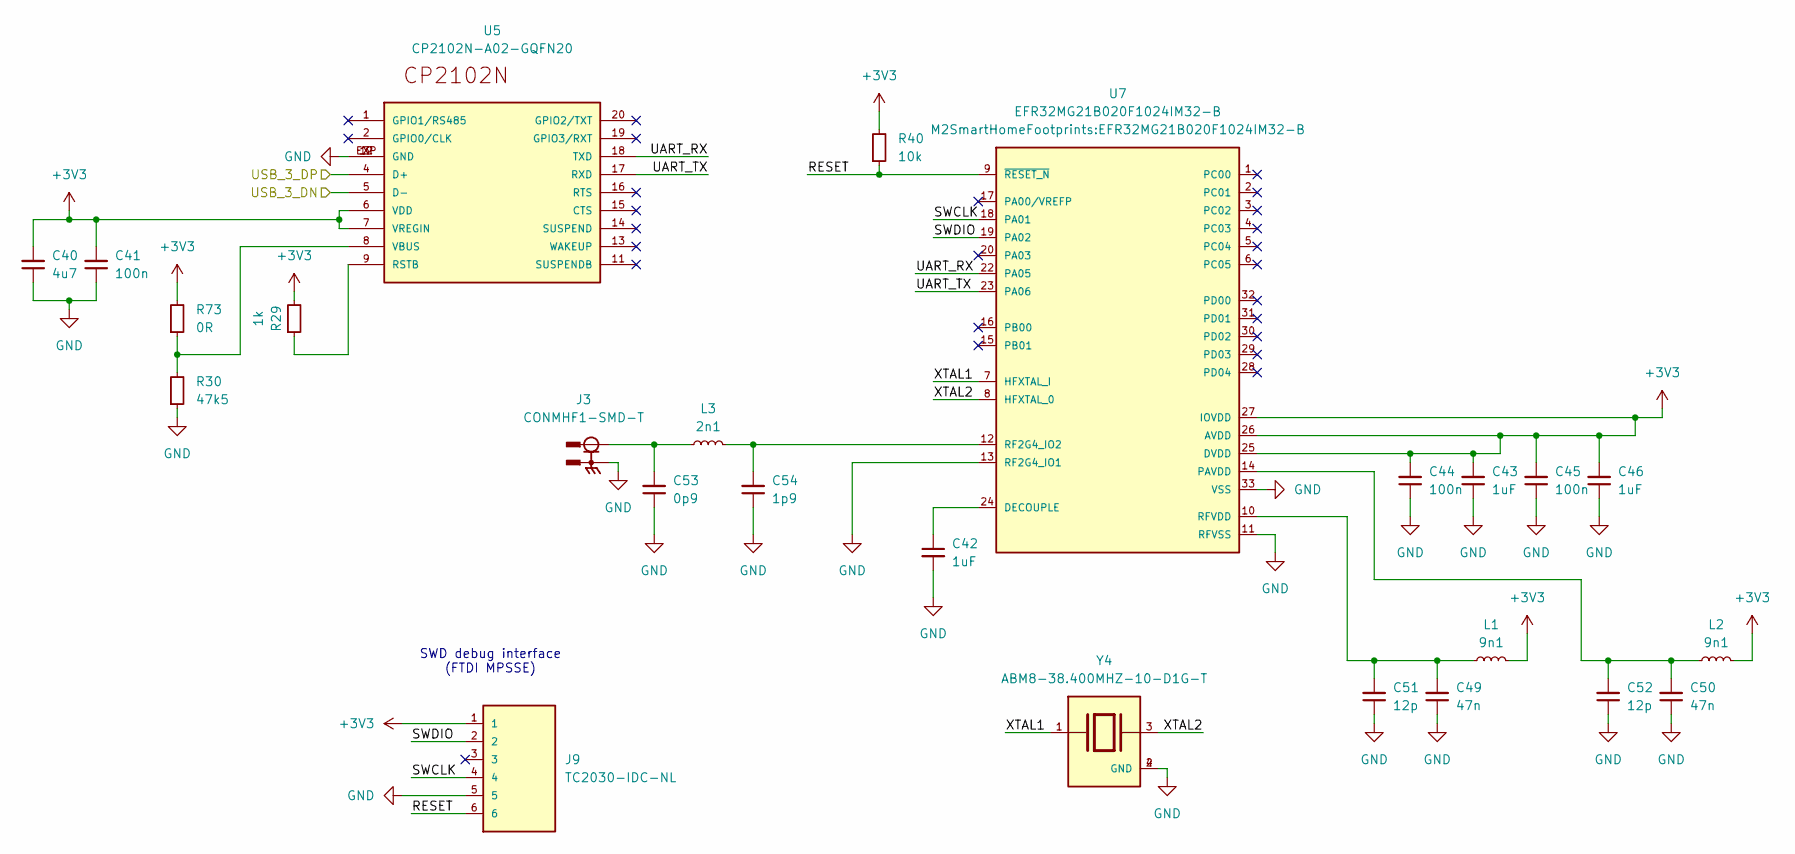
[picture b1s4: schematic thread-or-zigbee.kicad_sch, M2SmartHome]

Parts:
C40: C_4u7_0402; C_0402; Voltage 6.3V; MPN GRM155R60J475ME47D
C41, C44, C45: C_100n_0402; C_0402; Voltage 10V; MPN GRM155R61A104KA01D
C42, C43, C46: C_1uF_0402; C_0402; Voltage 50V; MPN GRM155R61H105KE05D
C49, C50: C_47n_0402; C_0402; Voltage 50V; MPN GRM155R61H473KE19D
C51, C52: C_12p_0402; C_0402; Voltage 50V; MPN GRM1555C1H120GA01D
C53: C_0p9_0201; C_0201; Voltage 50V; MPN GRM0335C1HR90WA01D
C54: C_1p9_0201; C_0201; Voltage 50V; MPN GRM0335C1H1R9WA01D
J3: CONMHF1-SMD-T
J9: TC2030-IDC-NL; TAG_TC2030-IDC-NL; PARTREV MS
L1, L2: L_9n1_0402; L_0402; MPN LQG15HS9N1J02D
L3: L_2n1_0201; L_0201; MPN LQP03HQ2N1B02D
R29: R_1k_0402; R_0402; Tolerance 1%; MPN CRCW04021K00FKED
R30: R_47k5_0402; R_0402; Tolerance 1%; MPN CRCW040247K5FKED
R40: R_10k_0402; R_0402; Tolerance 1%; MPN CRCW040210K0FKED
R73: R_0_0402; R_0402; MPN CRCW04020000Z0ED
U5: CP2102N-A02-GQFN20
U7: EFR32MG21B020F1024IM32-B
Y4: ABM8-38.400MHZ-10-D1G-T; XTAL_ABM8-38.400MHZ-10-D1G-T; PARTREV 44041

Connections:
+3V3: C40.2, C41.2, C43.2, C44.2, C45.2, C46.2, J9.1, L1.2, L2.2, R29.2, R40.2, R73.2, U5.6 (VDD), U5.7 (VREGIN), U7.25 (DVDD), U7.26 (AVDD), U7.27 (IOVDD); also elsewhere on the board
/pcie-usb-bridge/USB_3_DN: U5.5 (D-); also elsewhere on the board
/pcie-usb-bridge/USB_3_DP: U5.4 (D+); also elsewhere on the board
/thread-or-zigbee/RESET: J9.6, R40.1, U7.9 (~RESET_N)
/thread-or-zigbee/SWCLK: J9.4, U7.18 (PA01)
/thread-or-zigbee/SWDIO: J9.2, U7.19 (PA02)
/thread-or-zigbee/UART_RX: U5.18 (TXD), U7.22 (PA05)
/thread-or-zigbee/UART_TX: U5.17 (RXD), U7.23 (PA06)
/thread-or-zigbee/XTAL1: U7.7 (HFXTAL_I), Y4.1
/thread-or-zigbee/XTAL2: U7.8 (HFXTAL_0), Y4.3
GND: C40.1, C41.1, C42.2, C43.1, C44.1, C45.1, C46.1, C49.1, C50.1, C51.1, C52.1, C53.1, C54.1, J3.S1, J3.S2, J3.S3, J9.5, R30.1, U5.3 (GND), U5.12 (GND), U5.EXP (GND), U7.11 (RFVSS), U7.13 (RF2G4_IO1), U7.33 (VSS), Y4.2 (GND), Y4.4 (GND); also elsewhere on the board
unnamed: C53.2, J3.1, L3.1
unnamed: R29.1, U5.9 (RSTB)
unnamed: R30.2, R73.1, U5.8 (VBUS)
unnamed: C42.1, U7.24 (DECOUPLE)
unnamed: C50.2, C52.2, L2.1, U7.14 (PAVDD)
unnamed: C54.2, L3.2, U7.12 (RF2G4_IO2)
unnamed: C49.2, C51.2, L1.1, U7.10 (RFVDD)

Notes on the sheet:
SWD debug interface (FTDI MPSSE)

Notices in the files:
parts and their libraries:
License: Apache-2.0
